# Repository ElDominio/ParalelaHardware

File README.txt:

4-channel slim ECU with APM32F407VGT6, designed to use RusEFI

4 injection channel
4 ignition channels
additional outputs for boost/fuel pumps/idle/etc
onboard CAN
Hall or external VR conditioner
USB-C connection

No official firmware for this board (for now)

CPU pinout inside "Reference" folder

How to open EasyEDA Project File：

At editor, open the document via: Top menu - File - Open - EasyEDA... , and select the json file, then open it at the editor, you can save it into a project.

如何使用：

打开编辑器，通过：顶部菜单 - 文件 - 打开 - 立创EDA... ，选择 json 文件打开在编辑器，你可以保存文档进工程里面。

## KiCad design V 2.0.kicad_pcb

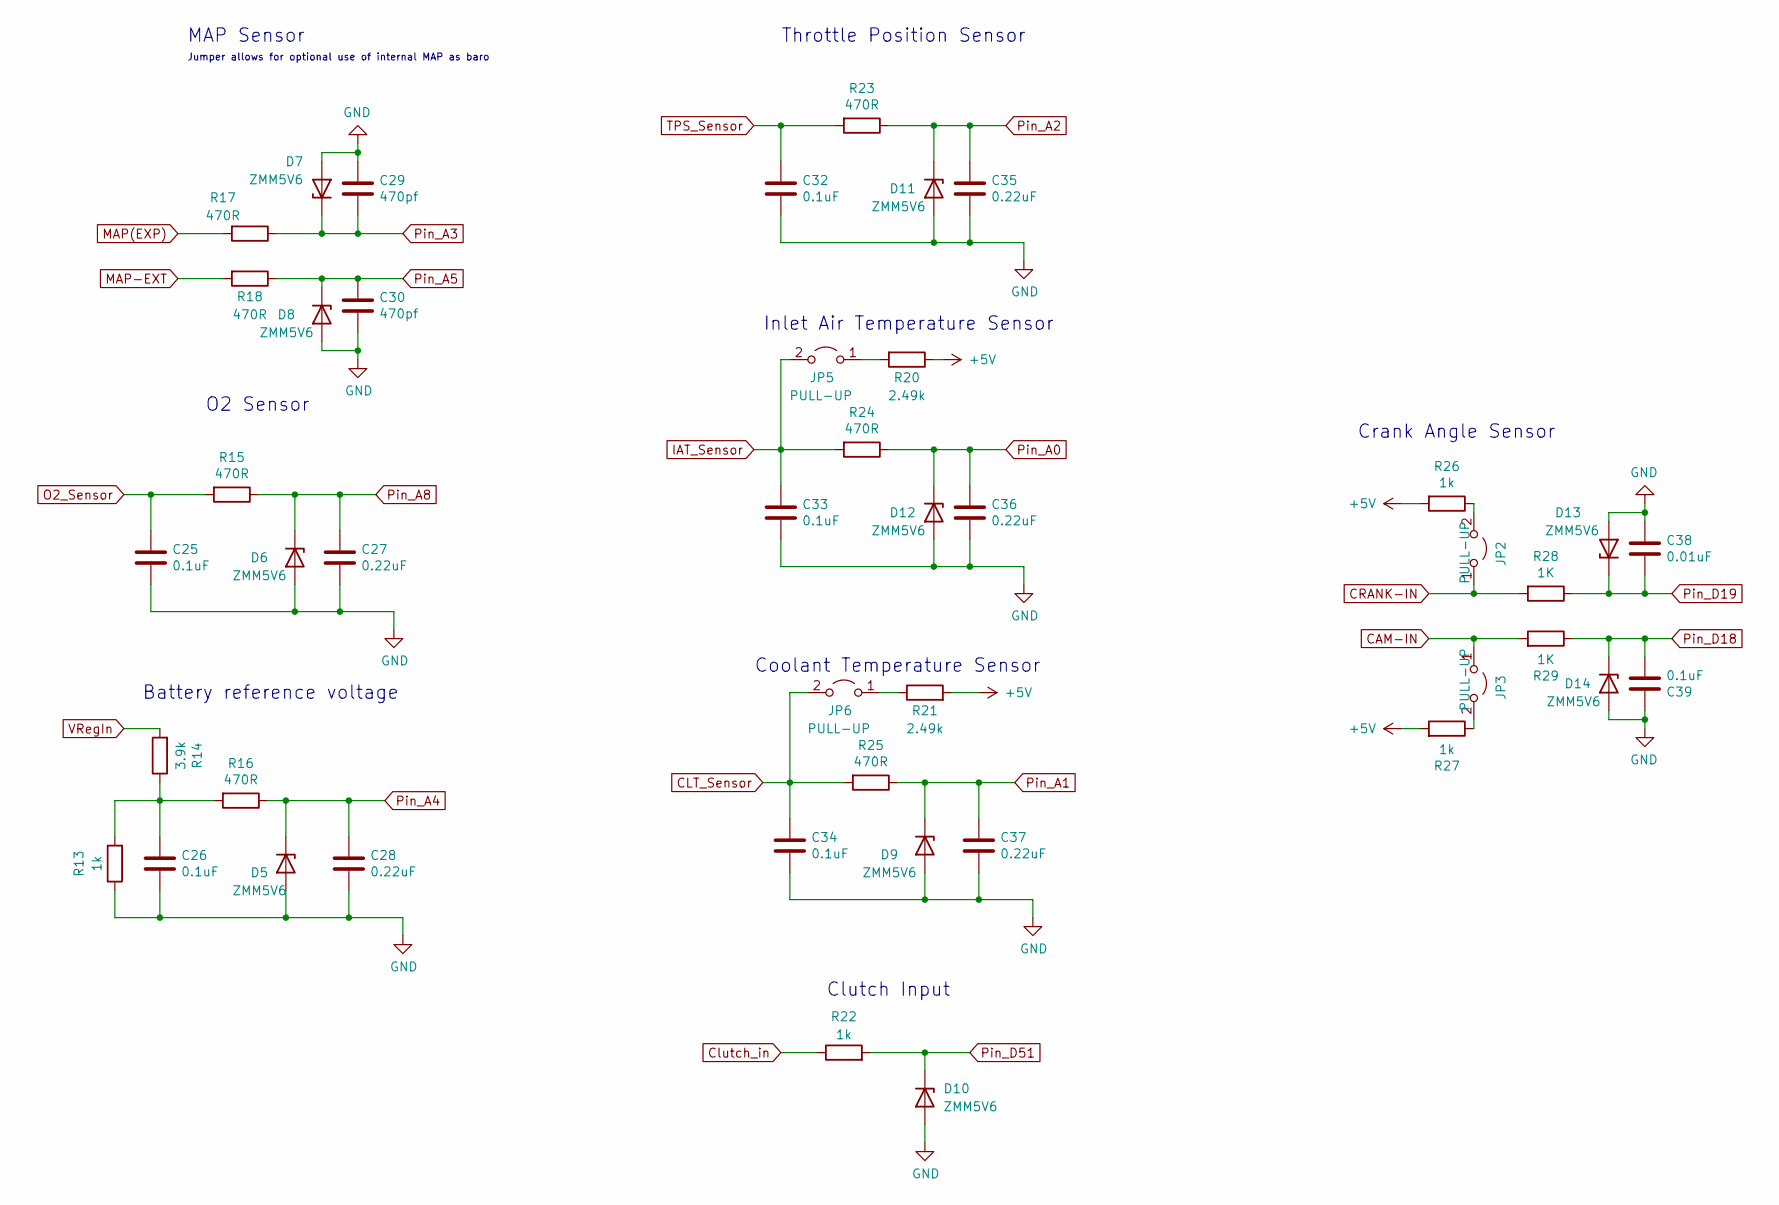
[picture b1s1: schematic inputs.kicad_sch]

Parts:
C25, C26, C32, C33, C34, C39: 0.1uF; C_0805_2012Metric; LCSC Part Number C49678
C27, C28, C35, C36, C37: 0.22uF; C_0805_2012Metric
C29, C30: 470pf; C_0805_2012Metric; LCSC Part Number C76630
C38: 0.01uF; C_0805_2012Metric
D5, D6, D7, D8, D9, D10, D11, D12, D13, D14: ZMM5V6; D_SOD-123; LCSC Part Number C8062
JP2, JP3: PULL-UP; PinHeader_1x02_P2.54mm_Vertical; LCSC Part Number C5116481
JP5, JP6: PULL-UP; SolderJumper-2_P1.3mm_Open_Pad1.0x1.5mm
R13, R22, R26, R27: 1k; R_0805_2012Metric; LCSC Part Number C408924
R14: 3.9k; R_0805_2012Metric; LCSC Part Number C171021
R15, R16, R17, R18, R23, R24, R25: 470R; R_0805_2012Metric; LCSC Part Number C229215
R20, R21: 2.49k; R_0805_2012Metric; LCSC Part Number C325835
R28, R29: 1K; R_0805_2012Metric; LCSC Part Number C416075

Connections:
+5V: R20.1, R21.2, R26.2, R27.2; also elsewhere on the board
CAM-IN: JP3.1 (A), R29.2; also elsewhere on the board
CLT_Sensor: C34.1, JP6.2 (B), R25.2; also elsewhere on the board
CRANK-IN: JP2.1 (A), R28.2; also elsewhere on the board
Clutch_in: R22.1; also elsewhere on the board
GND: C25.2, C26.2, C27.2, C28.2, C29.1, C30.2, C32.2, C33.2, C34.2, C35.2, C36.2, C37.2, C38.1, C39.1, D5.2 (A), D6.2 (A), D7.2 (A), D8.2 (A), D9.2 (A), D10.2 (A), D11.2 (A), D12.2 (A), D13.2 (A), D14.2 (A), R13.1; also elsewhere on the board
IAT_Sensor: C33.1, JP5.2 (B), R24.2; also elsewhere on the board
MAP(EXP): R17.2; also elsewhere on the board
MAP-EXT: R18.2; also elsewhere on the board
unnamed: C26.1, R13.2, R14.1, R16.2
unnamed: JP2.2 (B), R26.1
unnamed: JP3.2 (B), R27.1
unnamed: JP5.1 (A), R20.2
unnamed: JP6.1 (A), R21.1
O2_Sensor: C25.1, R15.2; also elsewhere on the board
Pin_A0: C36.1, D12.1 (K), R24.1; also elsewhere on the board
Pin_A1: C37.1, D9.1 (K), R25.1; also elsewhere on the board
Pin_A2: C35.1, D11.1 (K), R23.1; also elsewhere on the board
Pin_A3: C29.2, D7.1 (K), R17.1; also elsewhere on the board
Pin_A4: C28.1, D5.1 (K), R16.1; also elsewhere on the board
Pin_A5: C30.1, D8.1 (K), R18.1; also elsewhere on the board
Pin_A8: C27.1, D6.1 (K), R15.1; also elsewhere on the board
Pin_D18: C39.2, D14.1 (K), R29.1; also elsewhere on the board
Pin_D19: C38.2, D13.1 (K), R28.1; also elsewhere on the board
Pin_D51: D10.1 (K), R22.2; also elsewhere on the board
TPS_Sensor: C32.1, R23.2; also elsewhere on the board
VRegIn: R14.2; also elsewhere on the board

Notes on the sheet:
Coolant Temperature Sensor
Throttle Position Sensor
O2 Sensor
Inlet Air Temperature Sensor
Clutch Input
Battery reference voltage
Jumper allows for optional use of internal MAP as baro
MAP Sensor
Crank Angle Sensor

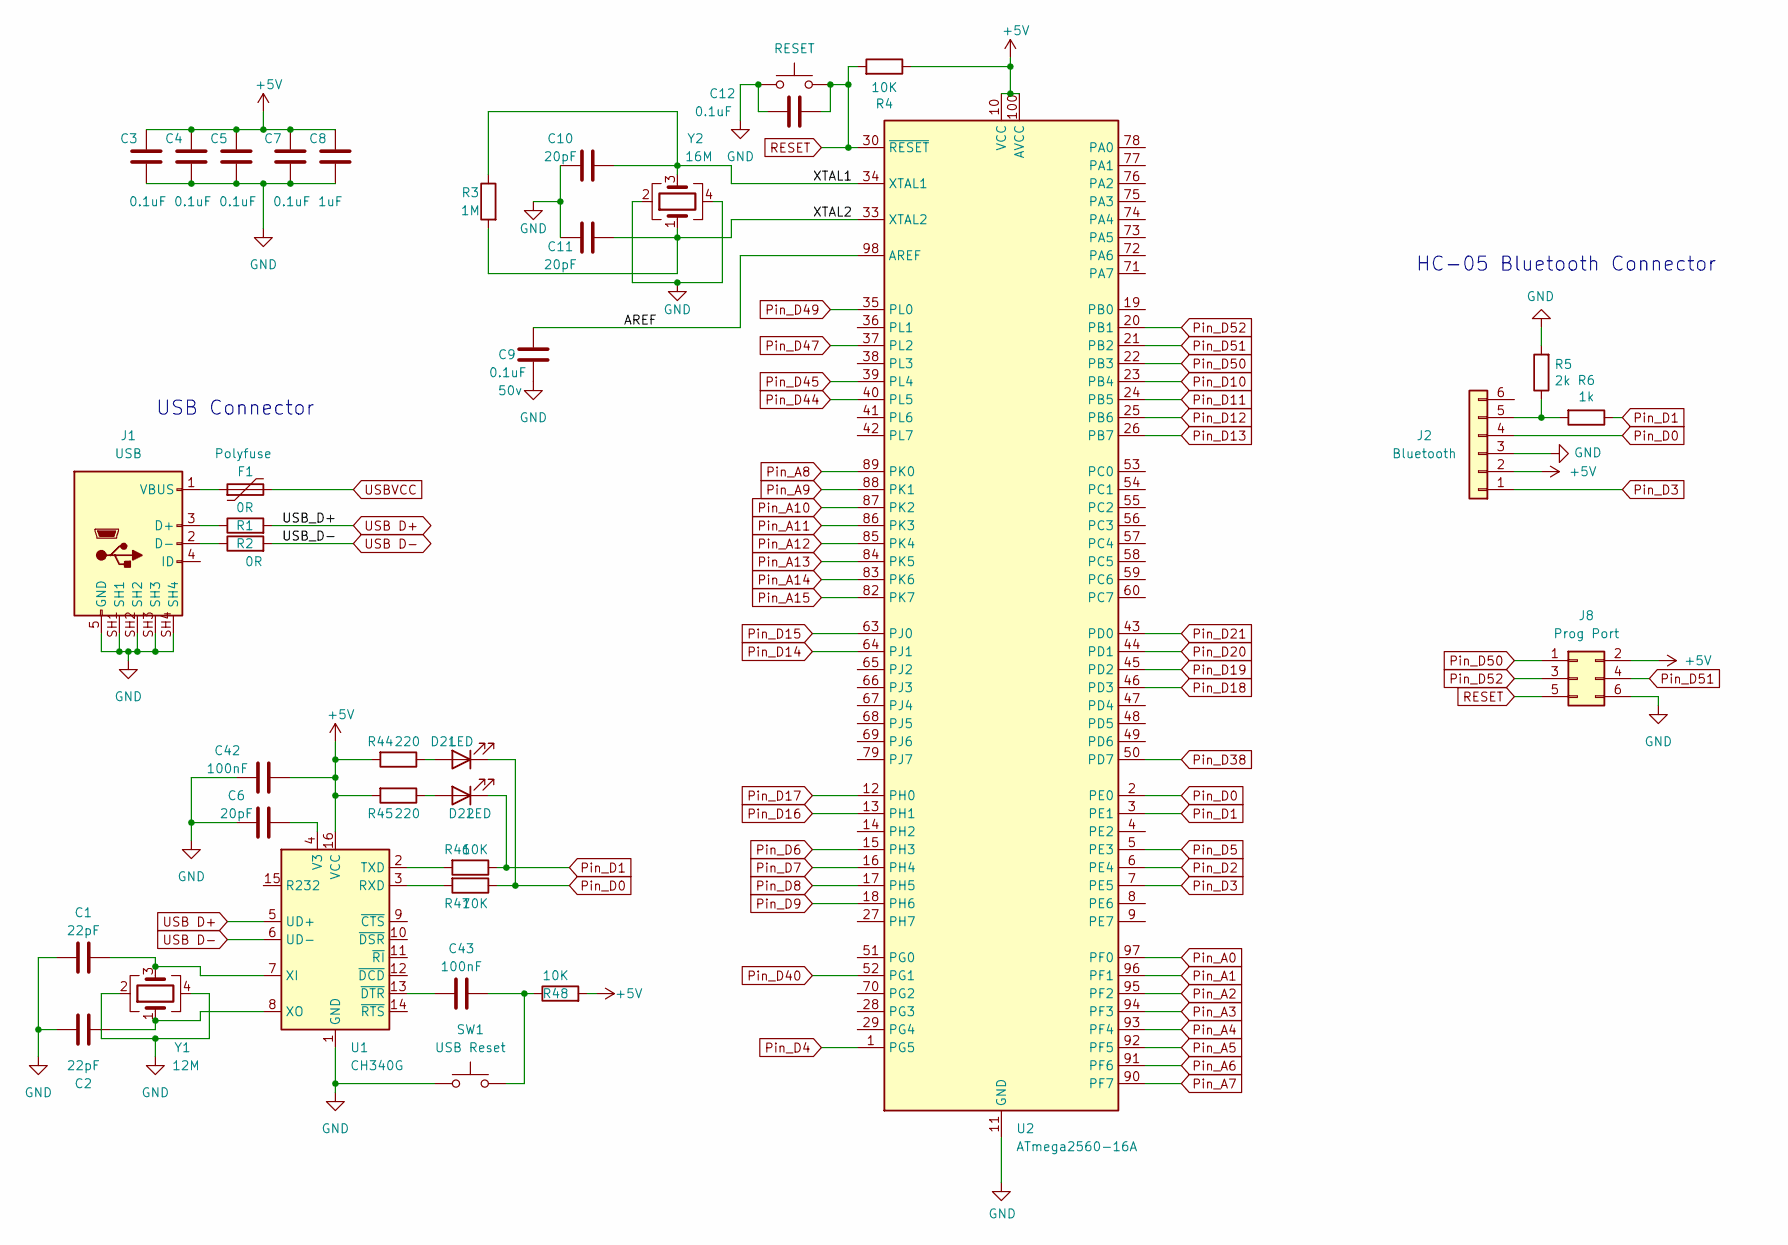
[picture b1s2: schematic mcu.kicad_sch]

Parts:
C1, C2: 22pF; C_0805_2012Metric; LCSC Part Number C149614
C3, C4, C5, C7, C12: 0.1uF; C_0805_2012Metric; LCSC Part Number C49678
C6, C10, C11: 20pF; C_0805_2012Metric; LCSC Part Number C149606
C8: 1uF; C_0805_2012Metric; LCSC Part Number C105952
C9: 0.1uF; C_0805_2012Metric; Voltage 50v; LCSC Part Number C49678
C42, C43: 100nF; C_0805_2012Metric; LCSC Part Number C495959
D21, D22: LED; LED_0805_2012Metric; LCSC Part Number C84256
F1: Polyfuse; Fuse_1812_4532Metric
J1: USB; USB Connector; LCSC Part Number C69074
J2: Bluetooth; PinHeader_1x06_P2.54mm_Vertical; LCSC Part Number C5156615
J8: Prog Port; PinHeader_2x03_P2.54mm_Vertical; LCSC Part Number C65114
R1, R2: 0R; R_0805_2012Metric; LCSC Part Number C728266
R3: 1M; R_0805_2012Metric; LCSC Part Number C416080
R4, R46, R47, R48: 10K; R_0805_2012Metric; LCSC Part Number C416062
R5: 2k; R_0805_2012Metric; LCSC Part Number C285226
R6: 1k; R_0805_2012Metric; LCSC Part Number C408924
R44, R45: 220; R_0805_2012Metric; LCSC Part Number C114519
RESET1: RESET; SW_Push_SPST_NO_Alps_SKRK
SW1: USB Reset; SW_Push_SPST_NO_Alps_SKRK
U1: CH340G; SOIC-16_3.9x9.9mm_P1.27mm; LCSC Part Number C14267
U2: ATmega2560-16A; TQFP-100_14x14mm_P0.5mm; LCSC Part Number C22460
Y1: 12M; Crystal_SMD_3225-4Pin_3.2x2.5mm; LCSC Part Number C9002
Y2: 16M; Crystal_SMD_3225-4Pin_3.2x2.5mm; LCSC Part Number C13738

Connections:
+5V: C3.2, C4.2, C5.2, C7.2, C8.2, C42.2, J2.2, J8.2, R4.1, R44.2, R45.2, R48.2, U1.16 (VCC), U2.10 (VCC), U2.31 (VCC), U2.61 (VCC), U2.80 (VCC), U2.100 (AVCC); also elsewhere on the board
/MCU/AREF: C9.1, U2.98 (AREF)
/MCU/XTAL1: C10.2, R3.1, U2.34 (XTAL1), Y2.3
/MCU/XTAL2: C11.2, R3.2, U2.33 (XTAL2), Y2.1
GND: C1.1, C2.1, C3.1, C4.1, C5.1, C6.1, C7.1, C8.1, C9.2, C10.1, C11.1, C12.2, C42.1, J1.5 (GND), J1.SH1, J1.SH2, J1.SH3, J1.SH4, J2.3, J8.6, R5.2, RESET1.1, SW1.1, U1.1 (GND), U2.11 (GND), U2.32 (GND), U2.62 (GND), U2.81 (GND), U2.99 (GND), Y1.2, Y1.4, Y2.2, Y2.4; also elsewhere on the board
unnamed: C1.2, U1.7 (XI), Y1.3
unnamed: C2.2, U1.8 (XO), Y1.1
unnamed: C6.2, U1.4 (V3)
unnamed: C43.1, U1.13 (~DTR)
unnamed: C43.2, R48.1, SW1.2
unnamed: D21.2 (A), R44.1
unnamed: D22.2 (A), R45.1
unnamed: F1.1, J1.1 (VBUS)
unnamed: J1.2 (D-), R2.1
unnamed: J1.3 (D+), R1.1
unnamed: J2.5, R5.1, R6.2
unnamed: R46.2, U1.2 (TXD)
unnamed: R47.2, U1.3 (RXD)
Pin_A0: U2.97 (PF0); also elsewhere on the board
Pin_A1: U2.96 (PF1); also elsewhere on the board
Pin_A2: U2.95 (PF2); also elsewhere on the board
Pin_A3: U2.94 (PF3); also elsewhere on the board
Pin_A4: U2.93 (PF4); also elsewhere on the board
Pin_A5: U2.92 (PF5); also elsewhere on the board
Pin_A6: U2.91 (PF6)
Pin_A7: U2.90 (PF7)
Pin_A8: U2.89 (PK0); also elsewhere on the board
Pin_A9: U2.88 (PK1); also elsewhere on the board
Pin_A10: U2.87 (PK2); also elsewhere on the board
Pin_A11: U2.86 (PK3)
Pin_A12: U2.85 (PK4)
Pin_A13: U2.84 (PK5)
Pin_A14: U2.83 (PK6)
Pin_A15: U2.82 (PK7)
Pin_D0: D21.1 (K), J2.4, R47.1, U2.2 (PE0)
Pin_D1: D22.1 (K), R6.1, R46.1, U2.3 (PE1)
Pin_D2: U2.6 (PE4); also elsewhere on the board
Pin_D3: J2.1, U2.7 (PE5)
Pin_D4: U2.1 (PG5); also elsewhere on the board
Pin_D5: U2.5 (PE3); also elsewhere on the board
Pin_D6: U2.15 (PH3); also elsewhere on the board
Pin_D7: U2.16 (PH4); also elsewhere on the board
Pin_D8: U2.17 (PH5); also elsewhere on the board
Pin_D9: U2.18 (PH6); also elsewhere on the board
Pin_D10: U2.23 (PB4); also elsewhere on the board
Pin_D11: U2.24 (PB5); also elsewhere on the board
Pin_D12: U2.25 (PB6)
Pin_D13: U2.26 (PB7)
Pin_D14: U2.64 (PJ1); also elsewhere on the board
Pin_D15: U2.63 (PJ0); also elsewhere on the board
Pin_D16: U2.13 (PH1)
Pin_D17: U2.12 (PH0)
Pin_D18: U2.46 (PD3); also elsewhere on the board
Pin_D19: U2.45 (PD2); also elsewhere on the board
Pin_D20: U2.44 (PD1); also elsewhere on the board
Pin_D21: U2.43 (PD0)
Pin_D38: U2.50 (PD7); also elsewhere on the board
Pin_D40: U2.52 (PG1); also elsewhere on the board
Pin_D44: U2.40 (PL5); also elsewhere on the board
Pin_D45: U2.39 (PL4); also elsewhere on the board
Pin_D47: U2.37 (PL2); also elsewhere on the board
Pin_D49: U2.35 (PL0); also elsewhere on the board
Pin_D50: J8.1, U2.22 (PB3); also elsewhere on the board
Pin_D51: J8.4, U2.21 (PB2); also elsewhere on the board
Pin_D52: J8.3, U2.20 (PB1); also elsewhere on the board
RESET: C12.1, J8.5, R4.2, RESET1.2, U2.30 (~RESET); also elsewhere on the board
USB D+: R1.2, U1.5 (UD+)
USB D-: R2.2, U1.6 (UD-)
USBVCC: F1.2; also elsewhere on the board

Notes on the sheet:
HC-05 Bluetooth Connector
USB Connector

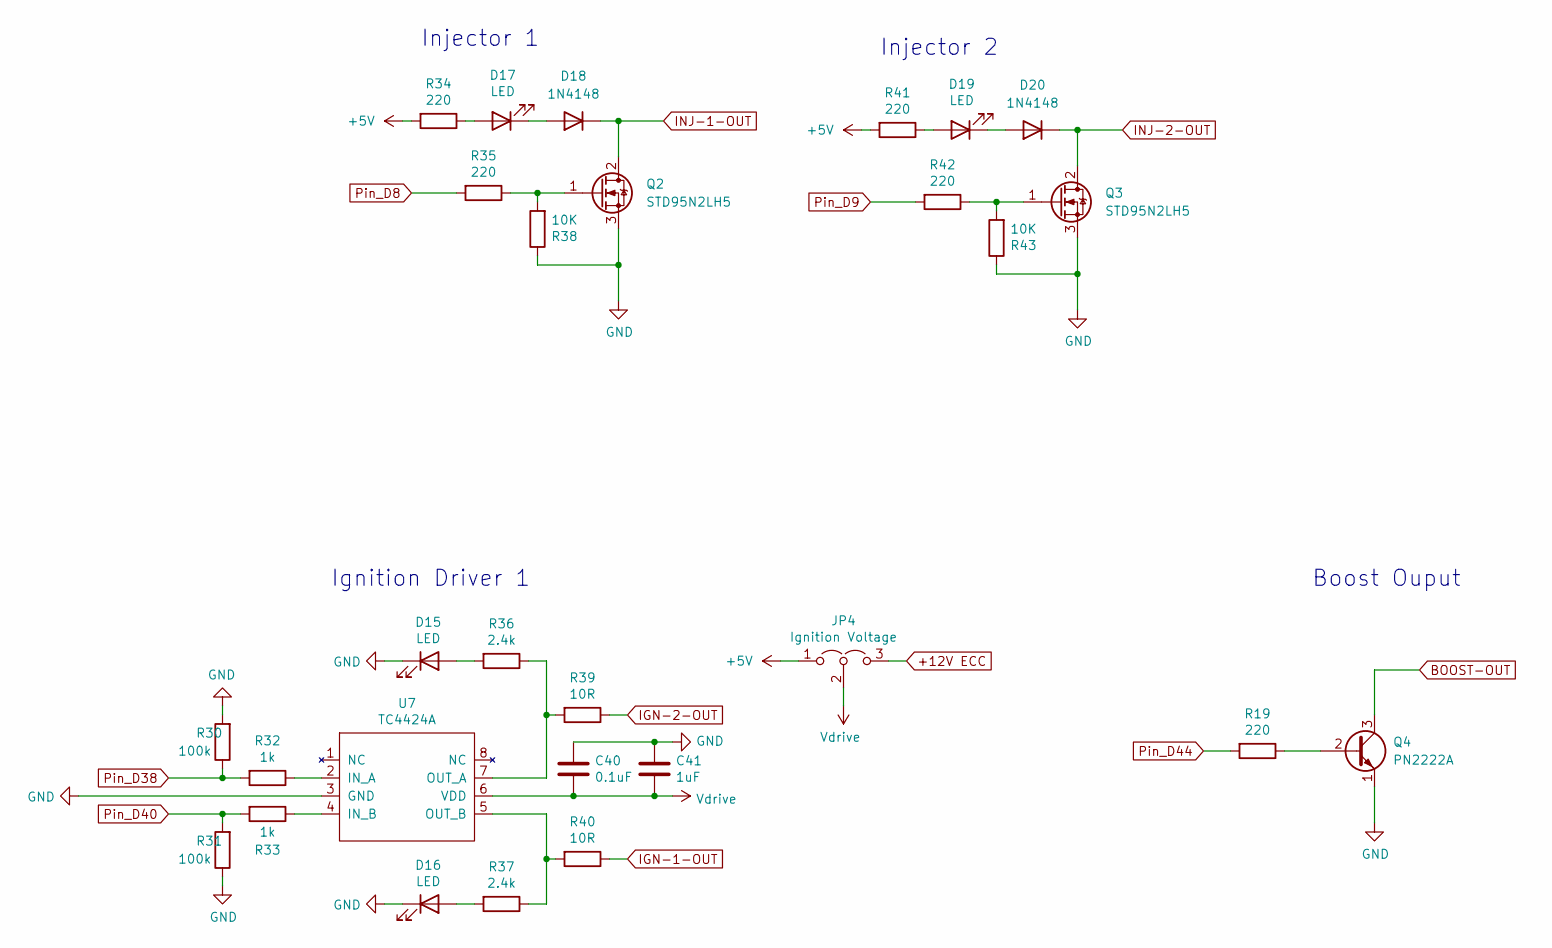
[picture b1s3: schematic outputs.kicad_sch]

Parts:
C40: 0.1uF; C_0805_2012Metric; LCSC Part Number C49678
C41: 1uF; C_0805_2012Metric; LCSC Part Number C105952
D15, D16, D17, D19: LED; LED_0805_2012Metric; LCSC Part Number C84256
D18, D20: 1N4148; D_0805_2012Metric_Pad1.15x1.40mm_HandSolder
JP4: Ignition Voltage; PinHeader_1x03_P2.54mm_Vertical; LCSC Part Number C306127
Q2, Q3: STD95N2LH5; TO-252-3_TabPin2; LCSC Part Number C155647
Q4: PN2222A; SOT-23; LCSC Part Number C80781
R19, R34, R35, R41, R42: 220; R_0805_2012Metric; LCSC Part Number C114519
R30, R31: 100k; R_0805_2012Metric; LCSC Part Number C416061
R32, R33: 1k; R_0805_2012Metric; LCSC Part Number C408924
R36, R37: 2.4k; R_0805_2012Metric; LCSC Part Number C325803
R38, R43: 10K; R_0805_2012Metric; LCSC Part Number C416062
R39, R40: 10R; R_0805_2012Metric; LCSC Part Number C212287
U7: TC4424A; SOIC-8_3.9x4.9mm_P1.27mm; LCSC Part Number C44150

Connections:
+5V: JP4.1 (A), R34.2, R41.2; also elsewhere on the board
+12V ECC: JP4.3 (B)
BOOST-OUT: Q4.3 (C); also elsewhere on the board
GND: C40.1, C41.1, D15.1 (K), D16.1 (K), Q2.3 (S), Q3.3 (S), Q4.1 (E), R30.2, R31.1, R38.1, R43.1, U7.3 (GND); also elsewhere on the board
IGN-1-OUT: R40.1; also elsewhere on the board
IGN-2-OUT: R39.1; also elsewhere on the board
INJ-1-OUT: D18.1 (K), Q2.2 (D); also elsewhere on the board
INJ-2-OUT: D20.1 (K), Q3.2 (D); also elsewhere on the board
unnamed: D15.2 (A), R36.2
unnamed: D16.2 (A), R37.2
unnamed: D17.1 (K), D18.2 (A)
unnamed: D17.2 (A), R34.1
unnamed: D19.1 (K), D20.2 (A)
unnamed: D19.2 (A), R41.1
unnamed: Q2.1 (G), R35.1, R38.2
unnamed: Q3.1 (G), R42.1, R43.2
unnamed: Q4.2 (B), R19.1
unnamed: R32.1, U7.2 (IN_A)
unnamed: R33.1, U7.4 (IN_B)
unnamed: R36.1, R39.2, U7.7 (OUT_A)
unnamed: R37.1, R40.2, U7.5 (OUT_B)
Pin_D8: R35.2; also elsewhere on the board
Pin_D9: R42.2; also elsewhere on the board
Pin_D38: R30.1, R32.2; also elsewhere on the board
Pin_D40: R31.2, R33.2; also elsewhere on the board
Pin_D44: R19.2; also elsewhere on the board
Vdrive: C40.2, C41.2, JP4.2 (C), U7.6 (VDD)

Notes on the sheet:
Ignition Driver 1
Boost Ouput
Injector 1
Injector 2

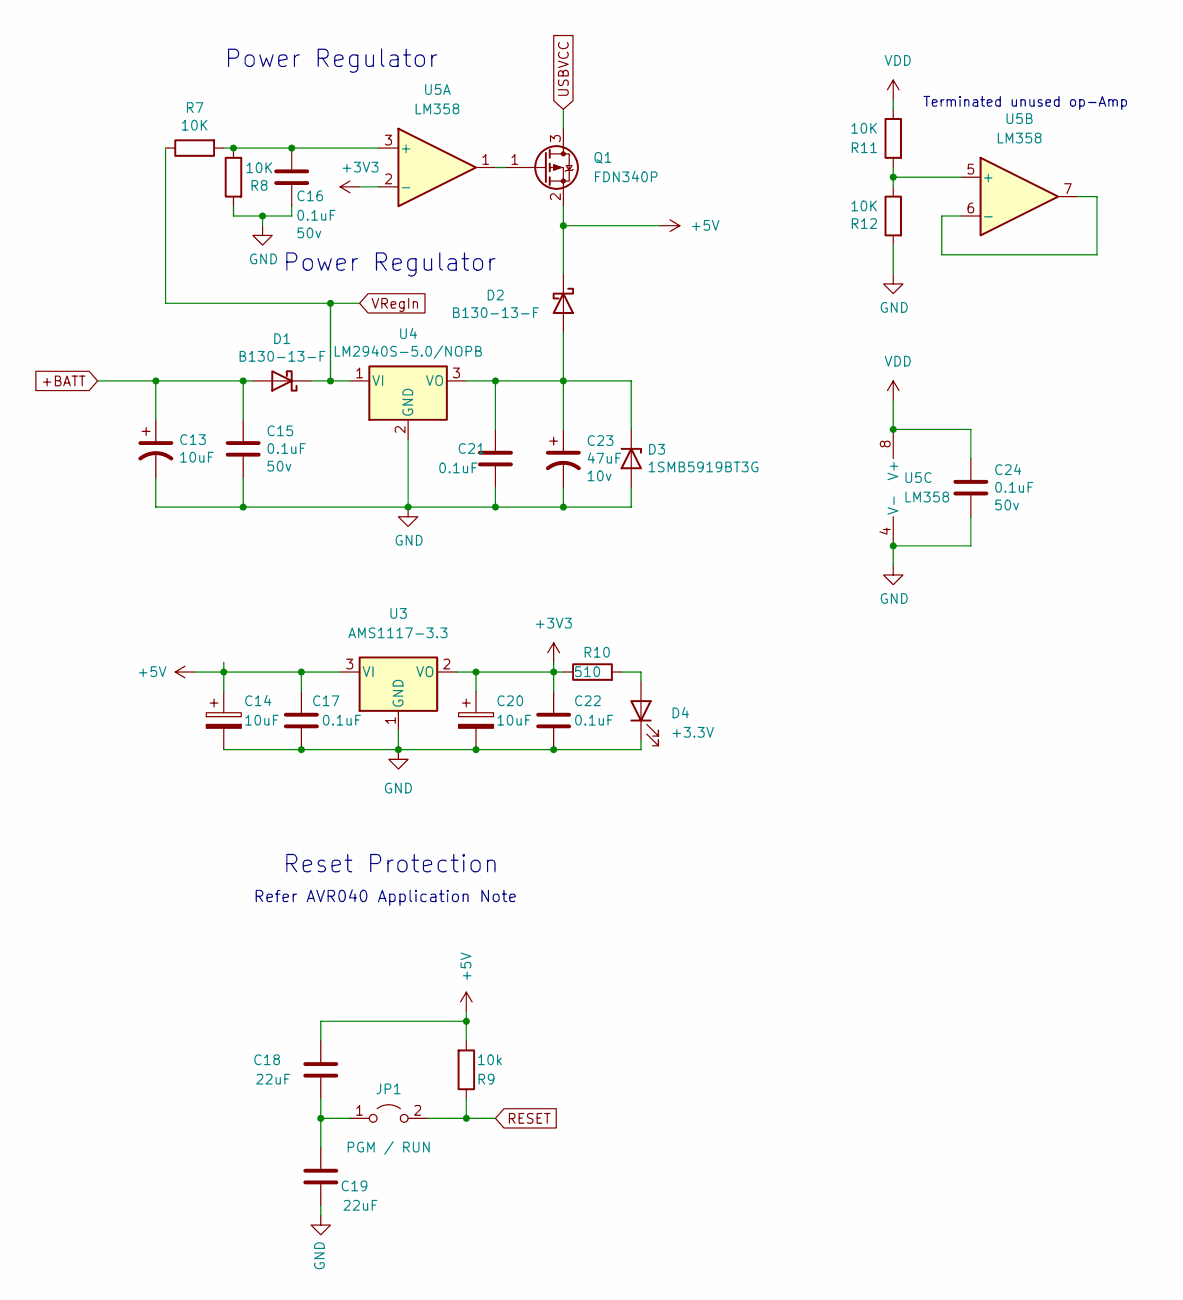
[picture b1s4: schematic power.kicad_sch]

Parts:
C13: 10uF; CP_EIA-7343-31_Kemet-D; Voltage 35v; LCSC Part Number C696821
C14, C20: 10uF; CP_EIA-3528-21_Kemet-B; LCSC Part Number C696821
C15, C16, C24: 0.1uF; C_0805_2012Metric; Voltage 50v; LCSC Part Number C49678
C17, C21, C22: 0.1uF; C_0805_2012Metric; LCSC Part Number C49678
C18, C19: 22uF; C_0805_2012Metric; LCSC Part Number C129303
C23: 47uF; CP_EIA-3528-21_Kemet-B; Voltage 10v
D1, D2: B130-13-F; D_SMA; LCSC Part Number C134423
D3: 1SMB5919BT3G; D_SMB; LCSC Part Number C70260
D4: +3.3V; LED_0805_2012Metric; LCSC Part Number C84256
JP1: PGM / RUN; PinHeader_1x02_P2.54mm_Vertical; LCSC Part Number C5116481
Q1: FDN340P; SOT-23; LCSC Part Number C2890122
R7, R8, R11, R12: 10K; R_0805_2012Metric; LCSC Part Number C416062
R9: 10k; R_0805_2012Metric; LCSC Part Number C416062
R10: 510; R_0805_2012Metric; LCSC Part Number C228886
U3: AMS1117-3.3; SOT-223-3_TabPin2; LCSC Part Number C2688239
U4: LM2940S-5.0/NOPB; SOT-223-3_TabPin2; LCSC Part Number C596334
U5: LM358; SOIC-8_3.9x4.9mm_P1.27mm; LCSC Part Number C16416

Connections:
+3V3: C20.1, C22.1, R10.1, U3.2 (VO), U5.2 (-)
+5V: C14.1, C17.1, C18.2, D2.1 (K), Q1.2 (S), R9.2, U3.3 (VI); also elsewhere on the board
+BATT: C13.1, C15.1, D1.2 (A); also elsewhere on the board
GND: C13.2, C14.2, C15.2, C16.2, C17.2, C19.1, C20.2, C21.2, C22.2, C23.2, C24.2, D3.2 (A), D4.1 (K), R8.2, R12.2, U3.1 (GND), U4.2 (GND), U5.4 (V-); also elsewhere on the board
unnamed: C16.1, R7.2, R8.1, U5.3 (+)
unnamed: C18.1, C19.2, JP1.1 (A)
unnamed: C21.1, C23.1, D2.2 (A), D3.1 (K), U4.3 (VO)
unnamed: D4.2 (A), R10.2
unnamed: Q1.1 (G), U5.1
unnamed: R11.2, R12.1, U5.5 (+)
unnamed: U5.6 (-), U5.7
RESET: JP1.2 (B), R9.1; also elsewhere on the board
USBVCC: Q1.3 (D); also elsewhere on the board
VDD: C24.1, R11.1, U5.8 (V+)
VRegIn: D1.1 (K), R7.1, U4.1 (VI); also elsewhere on the board

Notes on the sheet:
Power Regulator
Refer AVR040 Application Note
Reset Protection
Terminated unused op-Amp

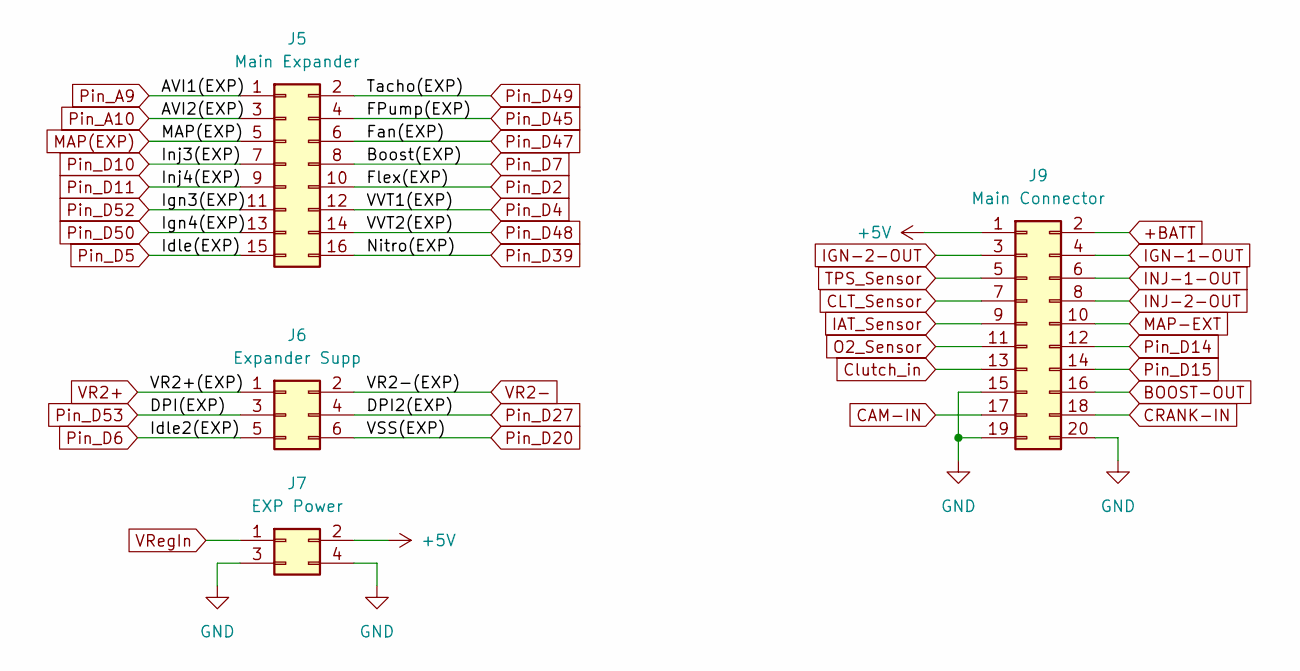
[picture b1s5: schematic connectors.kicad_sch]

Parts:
J5: Main Expander; Expansion 1; LCSC Part Number C917613
J6: Expander Supp; Expansion 2; LCSC Part Number C780054
J7: EXP Power; Expansion 3; LCSC Part Number C780055
J9: Main Connector; LCSC Part Number C169048

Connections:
+5V: J7.2, J9.1; also elsewhere on the board
+BATT: J9.2; also elsewhere on the board
BOOST-OUT: J9.16; also elsewhere on the board
CAM-IN: J9.17; also elsewhere on the board
CLT_Sensor: J9.7; also elsewhere on the board
CRANK-IN: J9.18; also elsewhere on the board
Clutch_in: J9.13; also elsewhere on the board
GND: J7.3, J7.4, J9.15, J9.19, J9.20; also elsewhere on the board
IAT_Sensor: J9.9; also elsewhere on the board
IGN-1-OUT: J9.4; also elsewhere on the board
IGN-2-OUT: J9.3; also elsewhere on the board
INJ-1-OUT: J9.6; also elsewhere on the board
INJ-2-OUT: J9.8; also elsewhere on the board
MAP(EXP): J5.5; also elsewhere on the board
MAP-EXT: J9.10; also elsewhere on the board
O2_Sensor: J9.11; also elsewhere on the board
Pin_A9: J5.1; also elsewhere on the board
Pin_A10: J5.3; also elsewhere on the board
Pin_D2: J5.10; also elsewhere on the board
Pin_D4: J5.12; also elsewhere on the board
Pin_D5: J5.15; also elsewhere on the board
Pin_D6: J6.5; also elsewhere on the board
Pin_D7: J5.8; also elsewhere on the board
Pin_D10: J5.7; also elsewhere on the board
Pin_D11: J5.9; also elsewhere on the board
Pin_D14: J9.12; also elsewhere on the board
Pin_D15: J9.14; also elsewhere on the board
Pin_D20: J6.6; also elsewhere on the board
Pin_D27: J6.4
Pin_D39: J5.16
Pin_D45: J5.4; also elsewhere on the board
Pin_D47: J5.6; also elsewhere on the board
Pin_D48: J5.14
Pin_D49: J5.2; also elsewhere on the board
Pin_D50: J5.13; also elsewhere on the board
Pin_D52: J5.11; also elsewhere on the board
Pin_D53: J6.3
TPS_Sensor: J9.5; also elsewhere on the board
VR2+: J6.1
VR2-: J6.2
VRegIn: J7.1; also elsewhere on the board

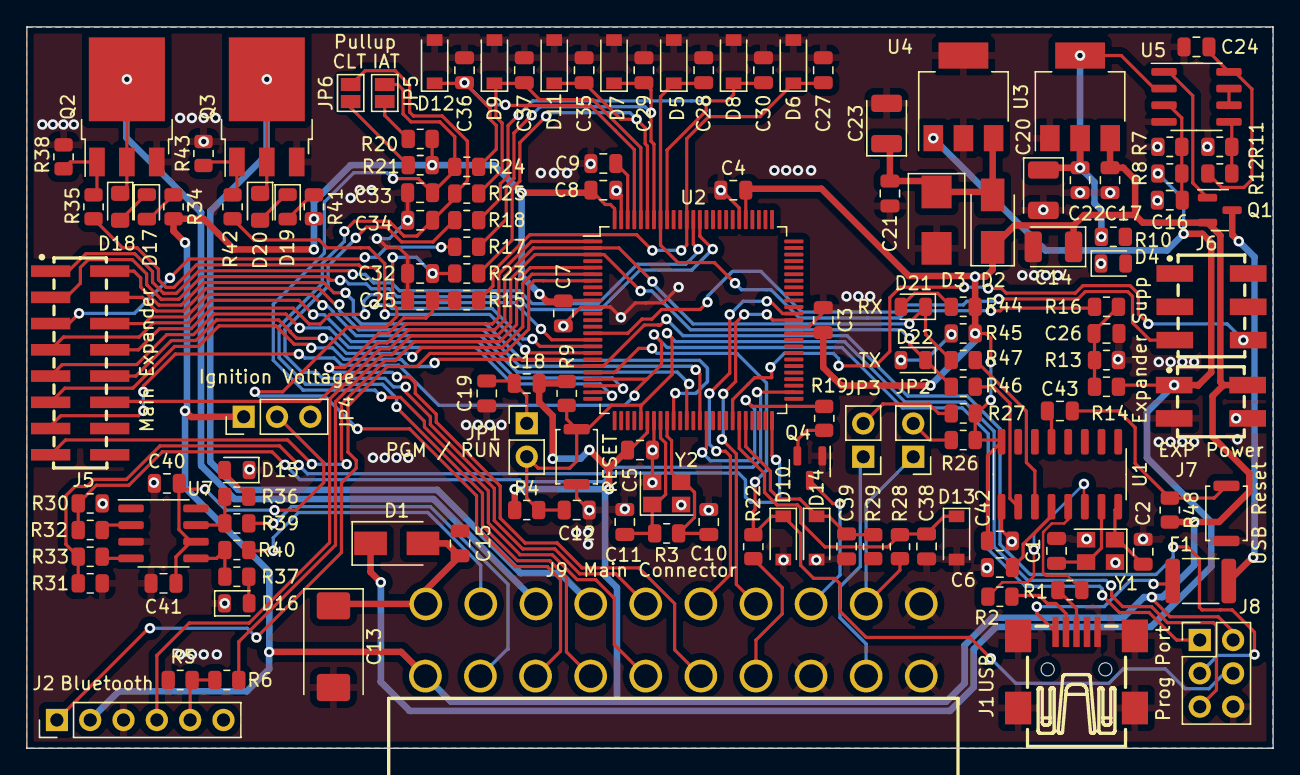
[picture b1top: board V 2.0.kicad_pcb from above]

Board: 2 copper layers, 95.0 x 55.0 mm, 140 parts (0 on the bottom side), 101 nets.

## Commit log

2022-11-23 Base design files
    All files to the AlphaECU Parallel are included
2022-11-23 TAPR License
2023-01-16 Mainboard Kicad files
2023-02-12 Added PDF schematics
2023-03-17 Paralela Hardware for RusEFI
    Full redesign for RusEFI compatiblity
    4x4 on board
2023-03-19 Inside a neat v1 folder
2023-03-19 Some extra details about the board
2023-03-19 WHere are CPU pins
2023-04-16 Attacked all present issues
    -add "alive" blue LED that is activated once firmware is properly loaded
    ADDED BLUE COMMS LED
    -use lower intensity LEDs for 5v and 12v
    ADDED HIGHER RESISTORS, TO LIMIT THE CURRENT TO 1MA, WHICH SHOULD BRING
    DOWN THE INTENSITY / BRIGHTNESS.
    -add diode on top layer for MCU power over USB
2023-09-19 V2 with fuel pump output fix
    Fuel pump did not work right, now fixed
